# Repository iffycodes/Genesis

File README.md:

# Genesis
Genesis Board design

## Change history

- Removed Stemma QT connectors. Left second LDO (AP2112-3.3). It looks to only be powering the neopixel on GPIO0. Need to figure out if I can just use the main one.
- Removed voltage divider used for LiPo monitoring. Provided A13_I35 that went to I35 on the ESP.
- Removed LiPo charging circuit. VBUS is now only supplied by USB-C connector. Removed DMG3415U transistor in upper left of Page 2. Removed JST battery connector.
- Removed extra reset switches.
- Add initial annotation.
- Rename +3V3 net on RTC page to match 3.3V global net name.
- Rename MISO nets on Ethernet page so global MISO net can go to buffer
- Remove second LDO. Power Neopixel from main regulator.
- Start adding heirarchical labels. Add notes to check sub-feather jumpers.
- Remove feather headers and ESP model from ETH and RTC pages.

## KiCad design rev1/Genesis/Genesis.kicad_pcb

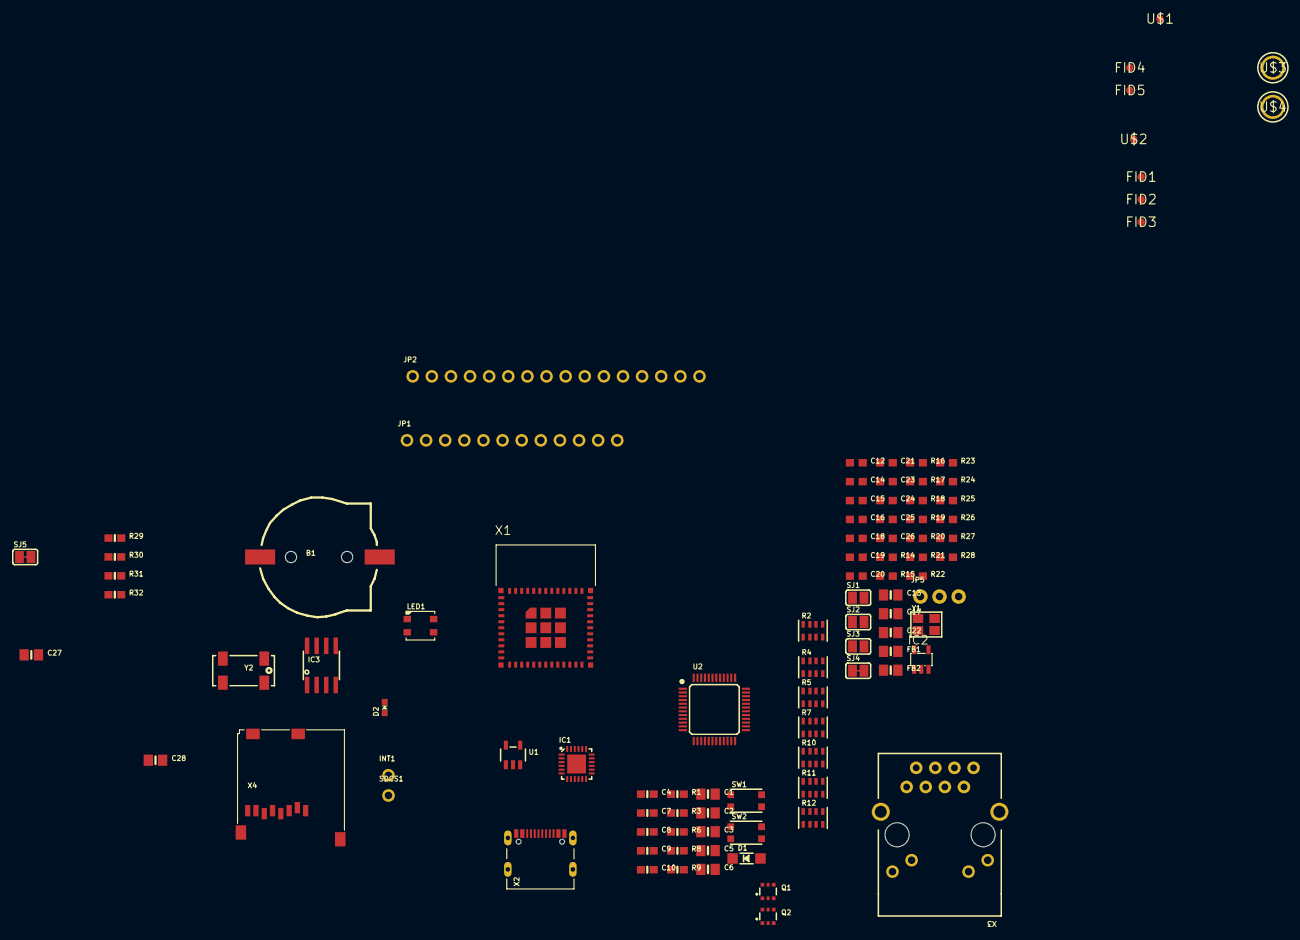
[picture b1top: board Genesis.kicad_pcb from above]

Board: 2 copper layers, 98 parts (0 on the bottom side), 74 nets, no tracks yet.

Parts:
B1: cr1220; CR1220-2
C1, C2: 10µF; 0805-NO
C3, C5, C6, C13, C17, C22, C27, C28: 10uF; 0805-NO
C4, C7, C9: 1uF; 0603-NO
C8, C10, C15, C16, C18, C19, C20, C21: 0.1uF; 0603-NO
C12, C14: 22pF; 0603-NO
C23, C26: 6.8nF; 0603-NO
C24, C25: 10nF; 0603-NO
D1: MBR540; SOD-123
D2: RED; CHIPLED_0603_NOOUTLINE
FB1, FB2: ferrite; 0805-NO
FID1, FID2, FID3: FIDUCIAL""; FIDUCIAL_1MM
FID4, FID5: FIDUCIAL_1MM
IC1: CP2102N-24; QFN24_4MM_SMSC
IC2: 74AHC1G125; SOT23-5L
IC3: PCF8523T; SOIC8_150MIL
INT1: HEADER-1X1ROUND; 1X01_ROUND
JP1: HEADER-1X12; 1X12_ROUND
JP2: HEADER-1X16ROUND; 1X16_ROUND
JP5: HEADER-1X376MIL; 1X03_ROUND_76
LED1: WS2812B3535; LED3535
Q1, Q2: DUAL NPN; SOT363
R1, R3, R30: 100K; 0603-NO
R2, R10, R11, R12: 47K; RESPACK_4X0603
R4, R5, R7: 10K; RESPACK_4X0603
R6, R8, R9: 5.1K; 0603-NO
R14: 1M; 0603-NO
R15, R18, R19, R20, R21, R28, R31, R32: 10K; 0603-NO
R16, R17: 470; 0603-NO
R22: 12.4K; 0603-NO
R23, R24, R25, R26: 49.9; 0603-NO
R27: 10; 0603-NO
R29: 1K; 0603-NO
SDCS1: HEADER-1X1ROUND; 1X01_ROUND
SJ1, SJ2, SJ3: SOLDERJUMPERREFLOW_NOPASTE; SOLDERJUMPER_REFLOW_NOPASTE
SJ4: SOLDERJUMPERCLOSED; SOLDERJUMPER_CLOSEDWIRE
SJ5: SOLDERJUMPER_CLOSED; SOLDERJUMPER_CLOSEDWIRE
SW1, SW2: KMR2; BTN_KMR2_4.6X2.8
U1: AP2112-3.3; SOT23-5
U2: W5500; LQFP48
U$1, U$2: FIDUCIAL_1MM
U$3, U$4: MOUNTINGHOLE2.5; MOUNTINGHOLE_2.5_PLATED
X1: ESP32-PICO-MINI-02MINI; ESP32-PICO-MINI
X2: USB Type C; USB_C_CUSB31-CFM2AX-01-X
X3: RB1-125BAG1A; RJ45_PULSEJACK
X4: microsd; MICROSD
Y1: 25MHz; CRYSTAL_3.2X2.5
Y2: 32khz; CRYSTAL_8X3.8

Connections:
3.3V: C2.1, C3.1, C4.1, C5.1, C6.1, C13.1, C15.1, C28.1, FB1.1, IC2.5 (VCC), JP2.15, LED1.2 (VDD), R2.8 (2), R7.1, R15.2, R18.1, R19.1, R20.1, R21.1, R28.2, R29.1, R30.2, R31.2, R32.2, U1.5 (OUT), U2.28 (VDD), X1.3 (3.3V), X3.10 (LED1_K), X3.12 (LED2_A), X4.4 (SD_VDD)
/ESP/3.45V: C8.1, C9.1, IC1.5 (VIO), IC1.6 (VDD)
/ESP/A0_DAC2: JP2.12, X1.16 (IO26/DAC2/A2_9)
/ESP/A1_DAC1: JP2.11, X1.15 (IO25/DAC1/A2_8)
/ESP/A2_I34: JP2.10, X1.9 (I34/A1_6)
/ESP/A3_I39: JP2.9, X1.7 (I39/A1_3)
/ESP/A4_I36: JP2.8, X1.4 (I36/A1_0)
/ESP/A5_IO4: JP2.7, X1.24 (IO4/A2_0)
/ESP/CC1: R9.2, X2.A5 (CC1)
/ESP/CC2: R8.2, X2.B5 (CC2)
/ESP/D+: IC1.3 (D+), X2.A6 (D+), X2.B6 (D+)
/ESP/D-: IC1.4 (D-), X2.A7 (D-), X2.B7 (D-)
/ESP/DTR: IC1.23 (DTR), Q1.1 (S), R5.1
/ESP/EN: JP1.2, R3.1, U1.3 (EN)
/ESP/GPIO0: LED1.1 (DI), Q1.6 (D), X1.23 (IO0/A2_1)
/ESP/I37: JP2.1, X1.5 (I37/A1_1)
/ESP/IO12_A11: JP1.5, X1.19 (IO12/A2_5)
/ESP/IO13_A12: JP1.4, R6.1, X1.20 (IO13/A2_4)
/ESP/IO14_A6: JP1.10, X1.18 (IO14/A2_6)
/ESP/IO15_A8: JP1.8, X1.21 (IO15/A2_3)
/ESP/IO27_A10: JP1.6, X1.17 (IO27/A2_7)
/ESP/IO32_A7: JP1.9, X1.12 (IO32/A1_4/X32P)
/ESP/IO33_A9: JP1.7, X1.13 (IO33/A1_5/X32N)
/ESP/MISO: IC2.4 (Y), JP2.4, X1.35 (IO21), X4.7 (DATA_OUT)
/ESP/MOSI: JP2.5, U2.35 (MOSI), X1.33 (IO19), X4.3 (DATA_IN)
/ESP/RTS: IC1.19 (RTS), Q2.1 (S), R4.8 (2)
/ESP/RXD0: IC1.21 (TXD), X1.30 (RXD0)
/ESP/RX/IO7: JP2.3, X1.27 (IO7)
/ESP/SCK: JP2.6, U2.33 (SCK), X1.29 (IO5), X4.5 (SCLK)
/ESP/SCL: IC3.6 (SCL), JP1.11, R31.1, X1.26 (IO20)
/ESP/SDA: IC3.5 (SDA), JP1.12, R32.1, X1.34 (IO22)
/ESP/TXD0: IC1.20 (RXD), X1.31 (TXD0)
/ESP/TX/IO8: JP2.2, X1.28 (IO8)
/ESP/VBUS_DET: IC1.8 (VBUS), R10.1, R11.1, R12.8 (2)
/ESP/VHI: C1.1, D1.C, R3.2, U1.1 (IN)
/ESP/~RESET: C7.1, JP2.16, Q2.6 (D), R7.8 (2), SW2.B (S), SW2.B' (S1), X1.8 (EN)
/Ethernet/CS: IC2.1 (~OE), JP5.1, R28.1, SJ4.1, U2.32 (SCSN)
/Ethernet/GREENLED: R17.1, X3.9 (LED1_A)
/Ethernet/IRQ: JP5.2, R15.1, U2.36 (INTN)
/Ethernet/MISO_W5500: IC2.2 (A), U2.34 (MISO)
/Ethernet/RESET: JP5.3, R18.2, U2.37 (RSTN)
/Ethernet/RX+: C23.2, R24.2, U2.6 (RXP)
/Ethernet/RX-: C26.2, R26.2, U2.5 (RXN)
/Ethernet/TX+: R25.1, U2.2 (TXP), X3.1 (TX+)
/Ethernet/TX-: R23.1, U2.1 (TXN), X3.2 (TX-)
/Ethernet/YELLOWLED: R16.1, X3.11 (LED2_K)
/RTC/CR1220: B1.+, IC3.3 (VBAT)
/RTC/INT1: IC3.7 (~INT1/CLK), INT1.1
/RTC/SD_CS: R30.1, SDCS1.1, SJ5.1, SJ5.2, X4.2 (CS)
AGND: C16.2, C17.2, C18.2, C19.2, C20.2, C21.2, C22.2, C24.2, C25.2, FB2.2, R22.2, U2.3 (AGND@1), U2.9 (AGND@2), U2.14 (AGND@4), U2.16 (AGND@5), U2.19 (AGND@6), U2.48 (AGND@7)
AVDD: C18.1, C19.1, C20.1, C21.1, C22.1, FB1.2, R23.2, R25.2, R27.2, U2.4 (AVDD@1), U2.8 (AVDD@2), U2.11 (AVDD@3), U2.15 (AVDD@4), U2.17 (AVDD@5), U2.21 (AVDD@6)
GND: B1.-, C1.2, C2.2, C3.2, C4.2, C5.2, C6.2, C7.2, C8.2, C9.2, C10.2, C12.2, C13.2, C14.2, C15.2, C27.2, C28.2, D2.C, FB2.1, IC1.2 (GND), IC1.THERM (GND), IC2.3 (GND), IC3.4 (VSS), JP2.13, LED1.4 (GND), R1.1, R8.1, R9.1, R12.1, SJ1.2, SJ2.2, SJ3.2, SW1.A, SW1.A' (P1), SW2.A, SW2.A' (P1), U1.2 (GND), U2.23 (RSVD(GND)), U2.29 (GND), X1.1 (GND), X1.2 (GND), X1.11 (GND), X1.14 (GND), X1.36 (GND), X1.37 (GND), X1.38 (GND), X1.39 (GND), X1.40 (GND), X1.41 (GND), X1.42 (GND), X1.43 (GND), X1.44 (GND), X1.45 (GND), X1.46 (GND), X1.47 (GND), X1.48 (GND), X1.49 (GND), X1.50 (GND), X1.51 (GND), X1.52 (GND), X1.53 (GND), X1.54 (GND), X1.55 (GND), X1.56 (GND), X1.57 (GND), X1.58 (GND), X1.59 (GND), X1.60 (GND), X1.61 (GND), X2.A1B12 (GND), X2.B1A12 (GND), X3.4 (GND1), X3.5 (GND2), X4.6 (GND@3), X4.MT1 (GND@2), X4.MT2 (GND@1)
unnamed: D2.A, R6.2
unnamed: C27.1, IC3.8 (VDD), R29.2
unnamed: IC3.1 (XI), Y2.P$4 (2)
unnamed: IC3.2 (XO), Y2.P$1 (1)
unnamed: Q1.2 (G), R4.1
unnamed: Q2.2 (G), R5.8 (2)
unnamed: R2.1, SW1.B (S), SW1.B' (S1), X1.6 (I38/A1_2)
unnamed: C16.1, U2.22 (1V20)
unnamed: R16.2, U2.27 (ACTLED)
unnamed: R22.1, U2.10 (EXRES1)
unnamed: R17.2, U2.25 (LINKLED)
unnamed: R21.2, SJ3.1, U2.45 (PMODE0)
unnamed: R20.2, SJ2.1, U2.44 (PMODE1)
unnamed: R19.2, SJ1.1, U2.43 (PMODE2)
unnamed: C17.1, U2.20 (TOCAP)
unnamed: C14.1, R14.2, U2.30 (XI/CLKIN), Y1.2
unnamed: C12.1, R14.1, U2.31 (XO), Y1.1
unnamed: C24.1, R24.1, R26.1, X3.6 (RCT)
unnamed: C23.1, X3.7 (RX+)
unnamed: C26.1, X3.8 (RX-)
unnamed: C25.1, R27.1, X3.3 (TCT)
VBUS: C10.1, D1.A, IC1.7 (REGIN), JP1.3, R1.2, R10.8 (2), R11.8 (2), X2.A4B9 (VBUS), X2.B4A9 (VBUS)

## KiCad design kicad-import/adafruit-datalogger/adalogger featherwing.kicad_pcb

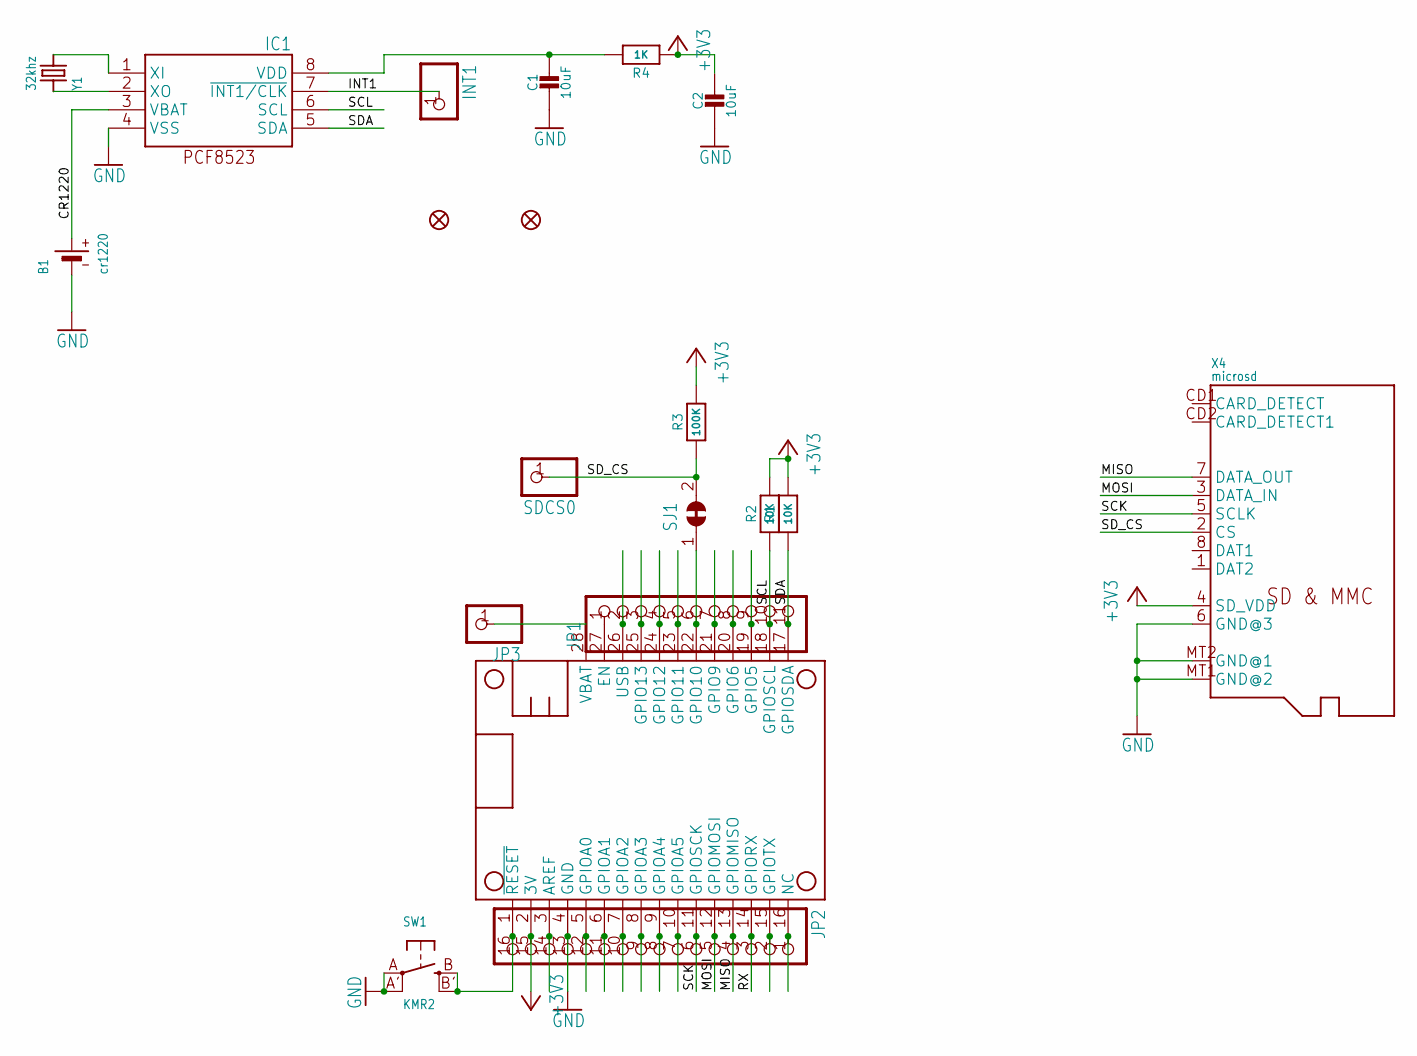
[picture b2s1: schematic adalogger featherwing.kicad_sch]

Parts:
B1: cr1220; CR1220-2
C1, C2: 10uF; 0805-NO
FID1, FID2: FIDUCIAL_1MM
IC1: PCF8523T; SOIC8_150MIL
INT1: HEADER-1X1ROUND; 1X01_ROUND
JP1: HEADER-1X11; 1X11_ROUND
JP2: HEADER-1X16ROUND; 1X16_ROUND
JP3: HEADER-1X1ROUND; 1X01_ROUND
MS1: FEATHERWING_NODIM
R1, R2: 10K; 0603-NO
R3: 100K; 0603-NO
R4: 1K; 0603-NO
SDCS0: HEADER-1X1ROUND; 1X01_ROUND
SJ1: SOLDERJUMPER_CLOSED; SOLDERJUMPER_CLOSEDWIRE
SW1: KMR2; BTN_KMR2_4.6X2.8
X4: microsd; MICROSD
Y1: 32khz; CRYSTAL_8X3.8

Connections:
+3V3: C2.1, JP2.15, MS1.2 (3V), R1.2, R2.2, R3.2, R4.1, X4.4 (SD_VDD)
A: JP2.12, MS1.5 (GPIOA0)
AREF: JP2.14, MS1.3 (AREF)
B: JP2.11, MS1.6 (GPIOA1)
C: JP2.10, MS1.7 (GPIOA2)
CR1220: B1.+, IC1.3 (VBAT)
CS: JP1.6, MS1.22 (GPIO10), SJ1.1
D: JP2.9, MS1.8 (GPIOA3)
E: JP2.8, MS1.9 (GPIOA4)
EN: JP1.1, MS1.27 (EN)
F: JP2.7, MS1.10 (GPIOA5)
G: JP2.1, MS1.16 (NC)
GND: B1.-, C1.2, C2.2, IC1.4 (VSS), JP2.13, MS1.4 (GND), SW1.A, SW1.A' (P1), X4.6 (GND@3), X4.MT1 (GND@2), X4.MT2 (GND@1)
H: JP1.9, MS1.19 (GPIO5)
I: JP1.8, MS1.20 (GPIO6)
INT1: IC1.7 (~INT1/CLK), INT1.1
J: JP1.7, MS1.21 (GPIO9)
L: JP1.5, MS1.23 (GPIO11)
M: JP1.4, MS1.24 (GPIO12)
MISO: JP2.4, MS1.13 (GPIOMISO), X4.7 (DATA_OUT)
MOSI: JP2.5, MS1.12 (GPIOMOSI), X4.3 (DATA_IN)
N: JP1.3, MS1.25 (GPIO13)
unnamed: C1.1, IC1.8 (VDD), R4.2
unnamed: IC1.1 (XI), Y1.P$4 (2)
unnamed: IC1.2 (XO), Y1.P$1 (1)
RESET: JP2.16, MS1.1 (~RESET), SW1.B (S), SW1.B' (S1)
RX: JP2.3, MS1.14 (GPIORX)
SCK: JP2.6, MS1.11 (GPIOSCK), X4.5 (SCLK)
SCL: IC1.6 (SCL), JP1.10, MS1.18 (GPIOSCL), R2.1
SDA: IC1.5 (SDA), JP1.11, MS1.17 (GPIOSDA), R1.1
SD_CS: R3.1, SDCS0.1, SJ1.2, X4.2 (CS)
TX: JP2.2, MS1.15 (GPIOTX)
USB: JP1.2, MS1.26 (USB)
VBAT: JP3.1, MS1.28 (VBAT)

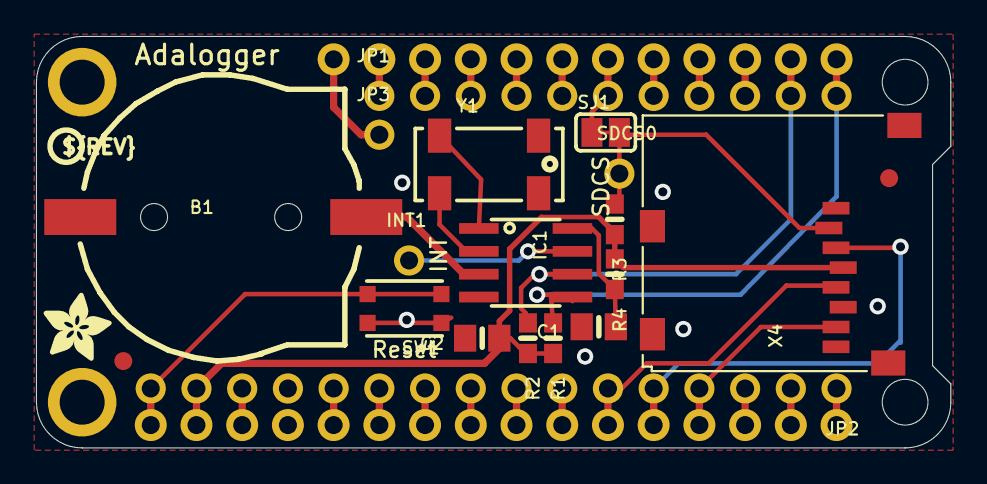
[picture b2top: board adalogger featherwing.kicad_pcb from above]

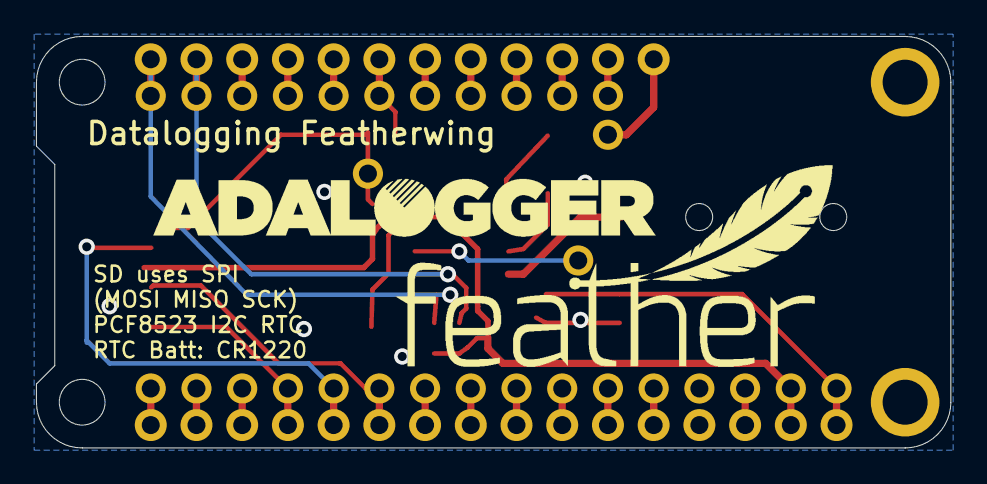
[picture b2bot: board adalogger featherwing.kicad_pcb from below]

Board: 2 copper layers, 50.8 x 22.9 mm, 24 parts (2 on the bottom side), 34 nets.

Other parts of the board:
U$2: FEATHERLOGO
U$3: ADALOGGER_LOGO
U$4: ADAFRUIT_3.5MM
U$5: PCBFEAT-REV-040

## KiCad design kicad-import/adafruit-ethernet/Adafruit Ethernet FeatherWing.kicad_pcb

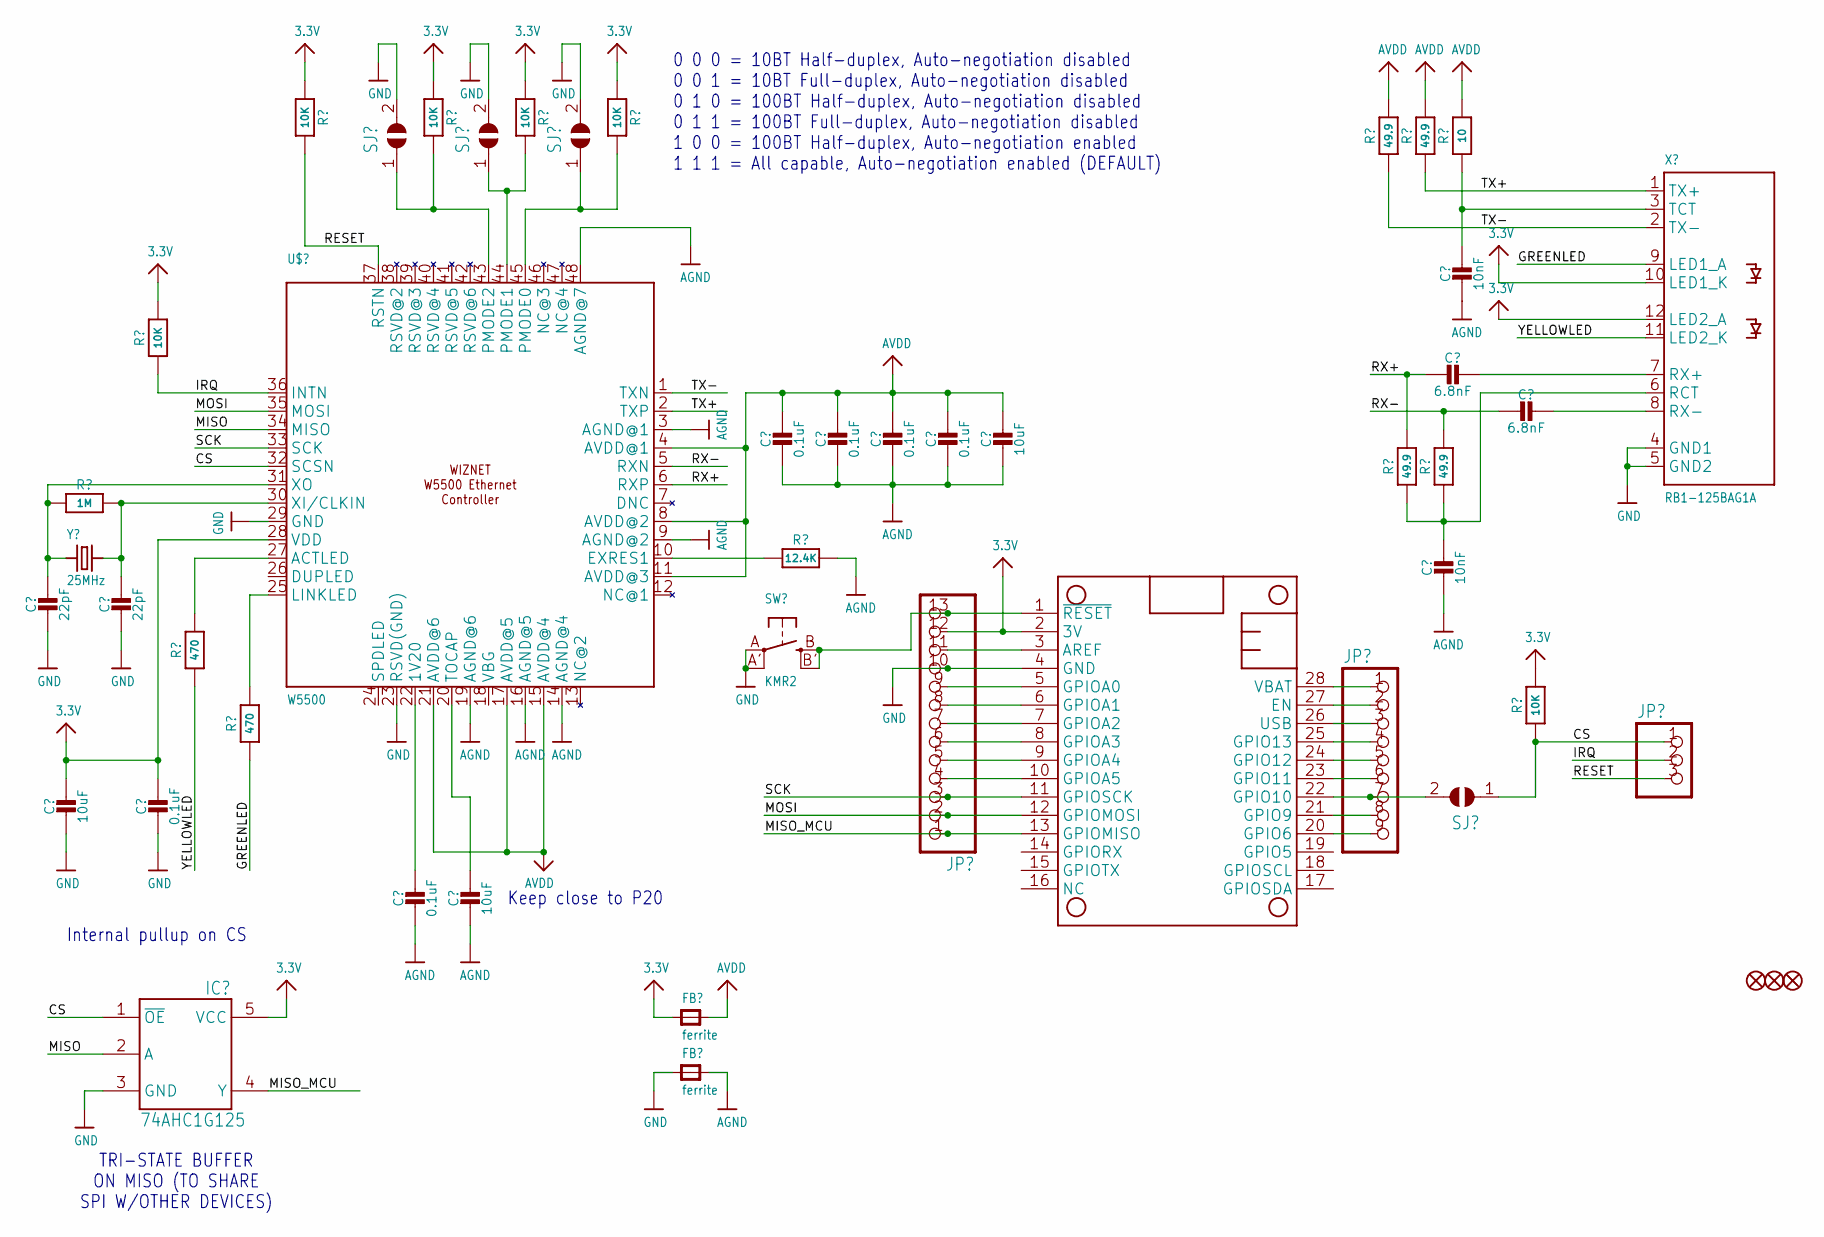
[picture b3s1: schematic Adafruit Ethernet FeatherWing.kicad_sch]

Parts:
C1, C2: 22pF; 0603-NO
C3, C4: 6.8nF; 0603-NO
C5, C6: 10nF; 0603-NO
C7, C8, C9, C10, C13, C15: 0.1uF; 0603-NO
C11, C12, C14: 10uF; 0805-NO
FB1, FB2: ferrite; 0805-NO
FID1, FID2, FID3: FIDUCIAL""; FIDUCIAL_1MM
IC1: 74AHC1G125; SOT23-5L
JP1: HEADER-1X376MIL; 1X03_ROUND_76
JP2: HEADER-1X13; 1X13_ROUND_70
JP4: HEADER-1X970MIL; 1X09_ROUND_70
MS1: FEATHERWING_NODIM
R1: 12.4K; 0603-NO
R2: 1M; 0603-NO
R3, R5, R6, R7, R8, R15: 10K; 0603-NO
R4, R9, R10, R11: 49.9; 0603-NO
R12: 10; 0603-NO
R13, R14: 470; 0603-NO
SJ1, SJ2, SJ3: SOLDERJUMPERREFLOW_NOPASTE; SOLDERJUMPER_REFLOW_NOPASTE
SJ4: SOLDERJUMPERCLOSED; SOLDERJUMPER_CLOSEDWIRE
SW1: KMR2; BTN_KMR2_4.6X2.8
U$1: W5500; LQFP48
X1: RB1-125BAG1A; RJ45_PULSEJACK
Y1: 25MHz; CRYSTAL_3.2X2.5

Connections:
3.3V: C14.1, C15.1, FB2.1, IC1.5 (VCC), JP2.12, MS1.2 (3V), R3.2, R5.1, R6.1, R7.1, R8.1, R15.2, U$1.28 (VDD), X1.10 (LED1_K), X1.12 (LED2_A)
AGND: C5.2, C6.2, C7.2, C8.2, C9.2, C10.2, C11.2, C12.2, C13.2, FB1.2, R1.2, U$1.3 (AGND@1), U$1.9 (AGND@2), U$1.14 (AGND@4), U$1.16 (AGND@5), U$1.19 (AGND@6), U$1.48 (AGND@7)
AVDD: C7.1, C8.1, C9.1, C10.1, C11.1, FB2.2, R4.2, R9.2, R12.2, U$1.4 (AVDD@1), U$1.8 (AVDD@2), U$1.11 (AVDD@3), U$1.15 (AVDD@4), U$1.17 (AVDD@5), U$1.21 (AVDD@6)
CS: IC1.1 (~OE), JP1.1, R15.1, SJ4.1, U$1.32 (SCSN)
GND: C1.2, C2.2, C14.2, C15.2, FB1.1, IC1.3 (GND), JP2.10, MS1.4 (GND), SJ1.2, SJ2.2, SJ3.2, SW1.A, SW1.A' (P1), U$1.23 (RSVD(GND)), U$1.29 (GND), X1.4 (GND1), X1.5 (GND2)
GREENLED: R14.1, X1.9 (LED1_A)
IRQ: JP1.2, R3.1, U$1.36 (INTN)
MISO: IC1.2 (A), U$1.34 (MISO)
MISO_MCU: IC1.4 (Y), JP2.1, MS1.13 (GPIOMISO)
MOSI: JP2.2, MS1.12 (GPIOMOSI), U$1.35 (MOSI)
unnamed: C1.1, R2.1, U$1.31 (XO), Y1.1
unnamed: C2.1, R2.2, U$1.30 (XI/CLKIN), Y1.2
unnamed: R1.1, U$1.10 (EXRES1)
unnamed: R5.2, SJ1.1, U$1.45 (PMODE0)
unnamed: R6.2, SJ2.1, U$1.44 (PMODE1)
unnamed: R7.2, SJ3.1, U$1.43 (PMODE2)
unnamed: C3.1, X1.7 (RX+)
unnamed: C4.1, X1.8 (RX-)
unnamed: C5.1, R10.1, R11.1, X1.6 (RCT)
unnamed: C6.1, R12.1, X1.3 (TCT)
unnamed: C13.1, U$1.22 (1V20)
unnamed: C12.1, U$1.20 (TOCAP)
unnamed: R13.2, U$1.27 (ACTLED)
unnamed: R14.2, U$1.25 (LINKLED)
unnamed: JP4.2, MS1.27 (EN)
unnamed: JP4.4, MS1.25 (GPIO13)
unnamed: JP4.5, MS1.24 (GPIO12)
unnamed: JP4.6, MS1.23 (GPIO11)
unnamed: JP4.7, MS1.22 (GPIO10), SJ4.2
unnamed: JP4.8, MS1.21 (GPIO9)
unnamed: JP4.9, MS1.20 (GPIO6)
unnamed: JP2.13, MS1.1 (~RESET), SW1.B (S), SW1.B' (S1)
unnamed: JP2.4, MS1.10 (GPIOA5)
unnamed: JP2.5, MS1.9 (GPIOA4)
unnamed: JP2.6, MS1.8 (GPIOA3)
unnamed: JP2.7, MS1.7 (GPIOA2)
unnamed: JP2.8, MS1.6 (GPIOA1)
unnamed: JP2.9, MS1.5 (GPIOA0)
unnamed: JP2.11, MS1.3 (AREF)
RESET: JP1.3, R8.2, U$1.37 (RSTN)
RX+: C3.2, R10.2, U$1.6 (RXP)
RX-: C4.2, R11.2, U$1.5 (RXN)
SCK: JP2.3, MS1.11 (GPIOSCK), U$1.33 (SCK)
TX+: R4.1, U$1.2 (TXP), X1.1 (TX+)
TX-: R9.1, U$1.1 (TXN), X1.2 (TX-)
USB: JP4.3, MS1.26 (USB)
VBAT: JP4.1, MS1.28 (VBAT)
YELLOWLED: R13.1, X1.11 (LED2_K)

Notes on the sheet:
Internal pullup on CS
Keep close to P20
TRI-STATE BUFFER ON MISO (TO SHARE SPI W/OTHER DEVICES)
0 0 0 = 10BT Half-duplex, Auto-negotiation disabled 0 0 1 = 10BT Full-duplex, Auto-negotiation disabled 0 1 0 = 100BT Half-duplex, Auto-negotiation disabled 0 1 1 = 100BT Full-duplex, Auto-negotiation disabled 1 0 0 = 100BT Half-duplex, Auto-negotiation enabled 1 1 1 = All capable, Auto-negotiation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

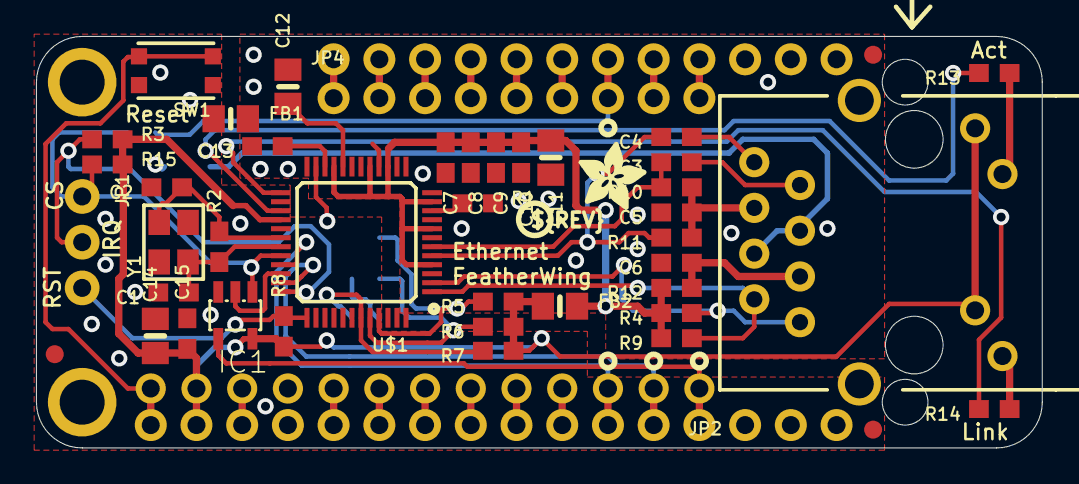
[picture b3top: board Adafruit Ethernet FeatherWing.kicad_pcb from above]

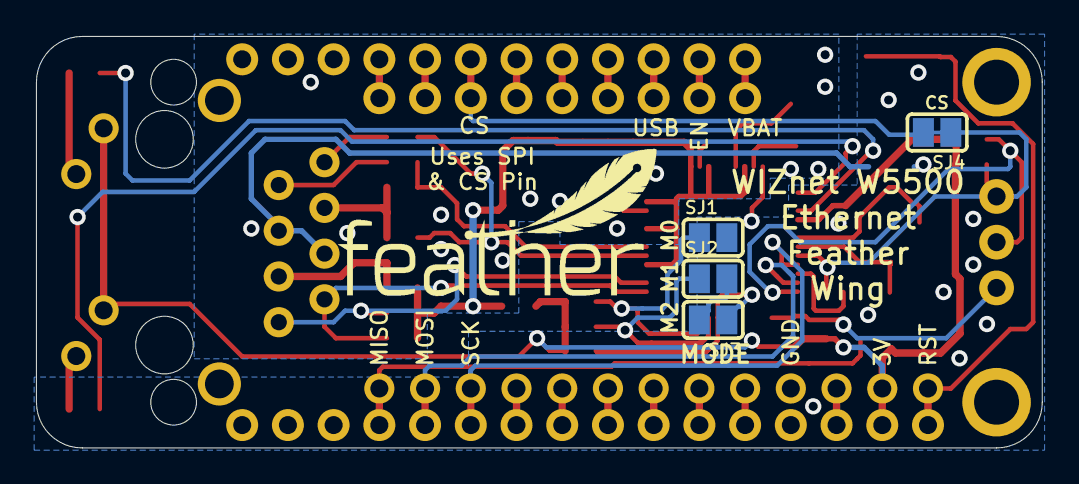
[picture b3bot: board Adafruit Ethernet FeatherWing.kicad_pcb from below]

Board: 2 copper layers, 55.9 x 22.9 mm, 51 parts (5 on the bottom side), 48 nets.

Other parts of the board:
U$45: PCBFEAT-REV-040
U$48: FEATHERLOGO_MED
U$49: ADAFRUIT_3.5MM

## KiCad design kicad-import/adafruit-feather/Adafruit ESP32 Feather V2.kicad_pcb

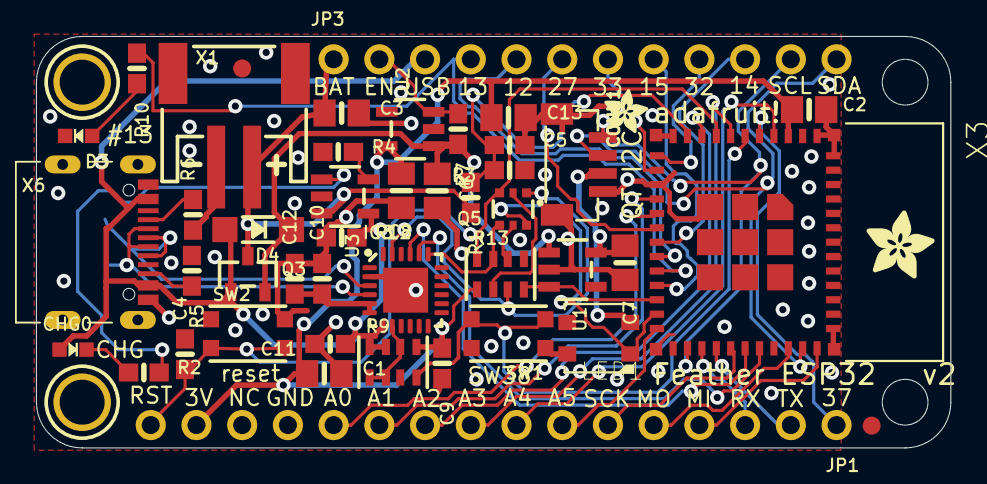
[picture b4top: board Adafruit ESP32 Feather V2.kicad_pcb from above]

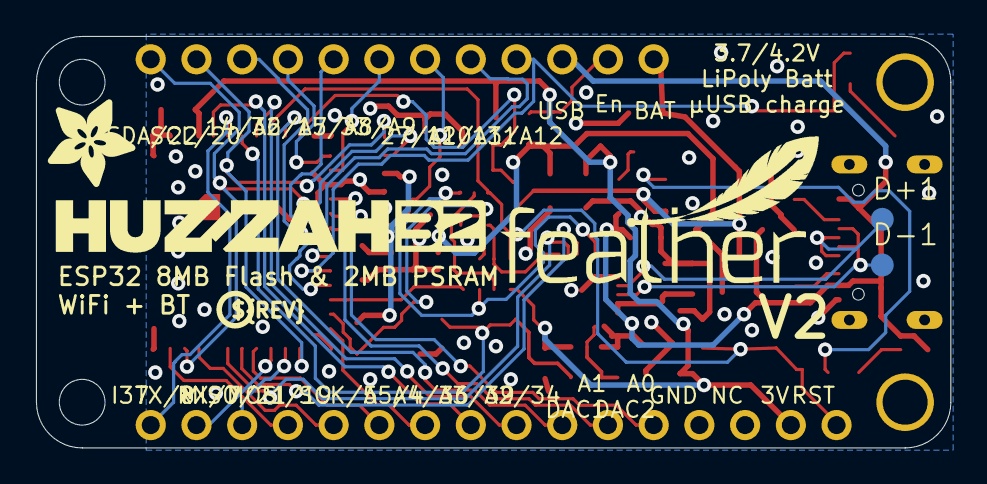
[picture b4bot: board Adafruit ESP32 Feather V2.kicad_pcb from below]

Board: 2 copper layers, 50.8 x 22.9 mm, 56 parts (6 on the bottom side), 49 nets.

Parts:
C1, C2, C13: 10uF; 0805-NO
C3, C6, C7, C8: 10µF; 0805-NO
C4, C5, C9, C10: 1uF; 0603-NO
C11, C12: 0.1uF; 0603-NO
CHG0: ORANGE; CHIPLED_0603_NOOUTLINE
CONN1: STEMMA_I2C_QTRA; JST_SH4_RA
D3: RED; CHIPLED_0603_NOOUTLINE
D4: MBR540; SOD-123
D+1: TPB1,27; B1,27_385
D-1: TPB1,27; B1,27_385
IC3: CP2102N-24; QFN24_4MM_SMSC
JP1: 1X16_ROUND
JP3: 1X12_ROUND
LED1: WS2812B3535; LED3535
Q3: DMG3415U; SOT23-R
Q5: DUAL NPN; SOT363
R1, R3: 200K; 0603-NO
R2, R4, R5, R6, R10: 5.1K; 0603-NO
R7, R12: 100K; 0603-NO
R9: 47K; RESPACK_4X0603
R13: 10K; RESPACK_4X0603
SW1, SW2: KMR2; BTN_KMR2_4.6X2.8
U1, U2: AP2112-3.3; SOT23-5
U3: MCP73831T-2ACI/OT; SOT23-5
U$7: ADAFRUIT_5MM
U$9: FEATHERLOGO_MED
U$13: PCBFEAT-REV-040
U$14: ADAFRUIT_2.5MM
U$15: ADAFRUIT_3.5MM
U$31, U$32: MOUNTINGHOLE2.5; MOUNTINGHOLE_2.5_PLATED
U$34, U$35: FIDUCIAL_1MM
U$43: HUZZAH32
UNK_HOLE_0: dummyfp0
UNK_HOLE_1: dummyfp1
X1: JSTPH; JSTPH2_BATT
X3: ESP32-PICO-MINI-02MINI; ESP32-PICO-MINI
X6: USB Type C; USB_C_CUSB31-CFM2AX-01-X

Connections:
3.3V: C1.1, C2.1, C8.1, C9.1, C13.1, JP1.15, R9.5, R13.1, U2.5, X3.3
3.45V: C10.1, C12.1, IC3.5, IC3.6
A0_DAC2: JP1.12, X3.16
A1_DAC1: JP1.11, X3.15
A2_I34: JP1.10, X3.9
A3_I39: JP1.9, X3.7
A4_I36: JP1.8, X3.4
A5_IO4: JP1.7, X3.24
A13_I35: C5.1, R1.1, R3.2, X3.10
CC1: R6.2, X6.A5
CC2: R5.2, X6.B5
D+: D+1.TP, IC3.3, X6.A6, X6.B6
D-: D-1.TP, IC3.4, X6.A7, X6.B7
DTR: IC3.23, Q5.1, R13.3
EN: JP3.2, R7.1, U2.3
GND: C1.2, C2.2, C3.2, C4.2, C5.2, C6.2, C7.2, C8.2, C9.2, C10.2, C11.2, C12.2, C13.2, CONN1.1, CONN1.MT1, CONN1.MT2, D3.C, IC3.2, IC3.THERM, JP1.13, LED1.4, R3.1, R4.1, R5.1, R6.1, R9.3, R12.1, R13.5, SW1.A, SW1.A', SW2.A, SW2.A', U1.2, U2.2, U3.2, X1.1, X1.NC1, X1.NC2, X3.1, X3.2, X3.11, X3.14, X3.36, X3.37, X3.38, X3.39, X3.40, X3.41, X3.42, X3.43, X3.44, X3.45, X3.46, X3.47, X3.48, X3.49, X3.50, X3.51, X3.52, X3.53, X3.54, X3.55, X3.56, X3.57, X3.58, X3.59, X3.60, X3.61, X6.A1B12, X6.B1A12
GPIO0: LED1.1, Q5.6, X3.23
I37: JP1.1, X3.5
IO12_A11: JP3.5, X3.19
IO13_A12: JP3.4, R10.1, X3.20
IO14_A6: JP3.10, X3.18
IO15_A8: JP3.8, X3.21
IO27_A10: JP3.6, X3.17
IO32_A7: JP3.9, X3.12
IO33_A9: JP3.7, X3.13
MISO: JP1.4, X3.35
MOSI: JP1.5, X3.33
unnamed: CHG0.C, R2.1
unnamed: R2.2, U3.1
unnamed: R4.2, U3.5
unnamed: D3.A, R10.2
unnamed: R9.4, SW1.B, SW1.B', X3.6
unnamed: Q5.5, R13.6
unnamed: Q5.2, R13.2
NEOI2C_PWR: R13.4, U1.3, X3.22
RTS: IC3.19, Q5.4, R13.7
RX/IO7: JP1.3, X3.27
RXD0: IC3.21, X3.30
SCK: JP1.6, X3.29
SCL: CONN1.4, JP3.11, X3.26
SDA: CONN1.3, JP3.12, X3.34
TX/IO8: JP1.2, X3.28
TXD0: IC3.20, X3.31
VBAT: C3.1, JP3.1, Q3.3, R1.2, U3.3, X1.2
VBUS: C11.1, CHG0.A, D4.A, IC3.7, JP3.3, Q3.1, R9.7, R9.8, R12.2, U3.4, X6.A4B9, X6.B4A9
VBUS_DET: IC3.8, R9.1, R9.2, R9.6
VHI: C6.1, D4.C, Q3.2, R7.2, U1.1, U2.1
V_NEOI2C: C7.1, CONN1.2, LED1.2, U1.5
~RESET: C4.1, JP1.16, Q5.3, R13.8, SW2.B, SW2.B', X3.8

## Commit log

2025-04-27 Initial commit.
2025-04-28 Remove Stemma QT connectors and LiPo circuitry. Update Notes.
2025-04-28 Update PDF schematic.
2025-04-29 Add initial annotation.
2025-04-29 Remove extra reset switches. Update notes.
2025-04-30 Change power net on RTC page to match global. Change buffered MISO net name on ETH PHY to allow global MISO.
2025-04-30 Update todo list and pdf schematic.
2025-05-01 Remove second LDO. Power Neopixel from main 3.3.
2025-05-01 Add note to check VDD pins on usb to serial convertor.
2025-05-06 Start adding heirarchical labels. Add notes to check sub-feather jumpers.
2025-05-06 Add cross-sheet nets for I2C.
2025-05-06 More updates.
2025-05-15 Add and connect SPI sheet labels to Ethernet page.
2025-05-22 Improve sheet labels. Remove extra model and headers from ETH and RTC pages.
2025-05-22 Some more net and label cleanup.
2025-05-22 Add KM logo to repo for silkscreen.
2025-05-23 Update logo colors for silkscreen.
2025-05-27 Initial sheet settings for layout.
2025-06-17 Add imported symbol libraries to project
2025-06-17 Add footprint libraries to project
2025-06-18 Do rough major component placement for layout
